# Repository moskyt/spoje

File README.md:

# Spoje

## Hardware

### Napajeni

vsechna ctyri napeti maji svoji indikaci na prednim panelu a svuj vypinac

na vstupnich 230VAC je pojistka

POZOR! IEC konektor na vstupu nema standardizovane zapojeni, resp. ruzne kabely jsou ruzne. je tedy treba mit na pameti, ze L a N mohou byt prohozene (a nikdo s tim nic neudela)

### DC

Meanwell RD-35B (+5/+24V)

5V napaji arduino

24V napaji telefonni linku

### Trafo

pouziva se pro vyzvaneci AC

je to trafo 400->110, tedy 230->63 voltu, coz je optimalni

### Zapojeni

viz `spoje_pcb` -- projekt v kicadu

v 'doc/` je vyexportovane schema a PCB v kicadu

vsechny draty jsou popsane

## Ovladani

### Vypinace

napajeni ctyr napeti (master 230VAC, vyzvaneci trafo, dva vystupy z DC zdroje)

cervene reset tlacitko (hardware reset na RESET pinu)

### Zvoneni

zluta tlacitka jsou na vyzvaneni na prislusnych linkach. je to SW zvoneni, aktivace stavu POKE.

## Literatura

specifikace vyzvanecich tonu:

https://www.ctu.cz/sites/default/files/obsah/clanky/navrh-sitoveho-planu-signalizace-verejnych-telekomunikacnich-siti-poskytujicich-verejne-dostupnou/soubory/priloha-7-specifikace-tonu-1113656123.pdf

https://vyvoj.hw.cz/navrh-obvodu/rozhrani/telefonni-linky-v-cr-a-sr.html

https://www.ranecommercial.com/legacy/note150.html

http://home.zcu.cz/~vargaj/U%20S%20T/Telefonni%20pristroje.pdf

http://mcu.cz/news.php?extend.8
http://mcu.cz/images/newspost_images/00/26/00-26.pdf

https://forum.arduino.cc/t/intercom-using-two-old-dial-telephones/606457

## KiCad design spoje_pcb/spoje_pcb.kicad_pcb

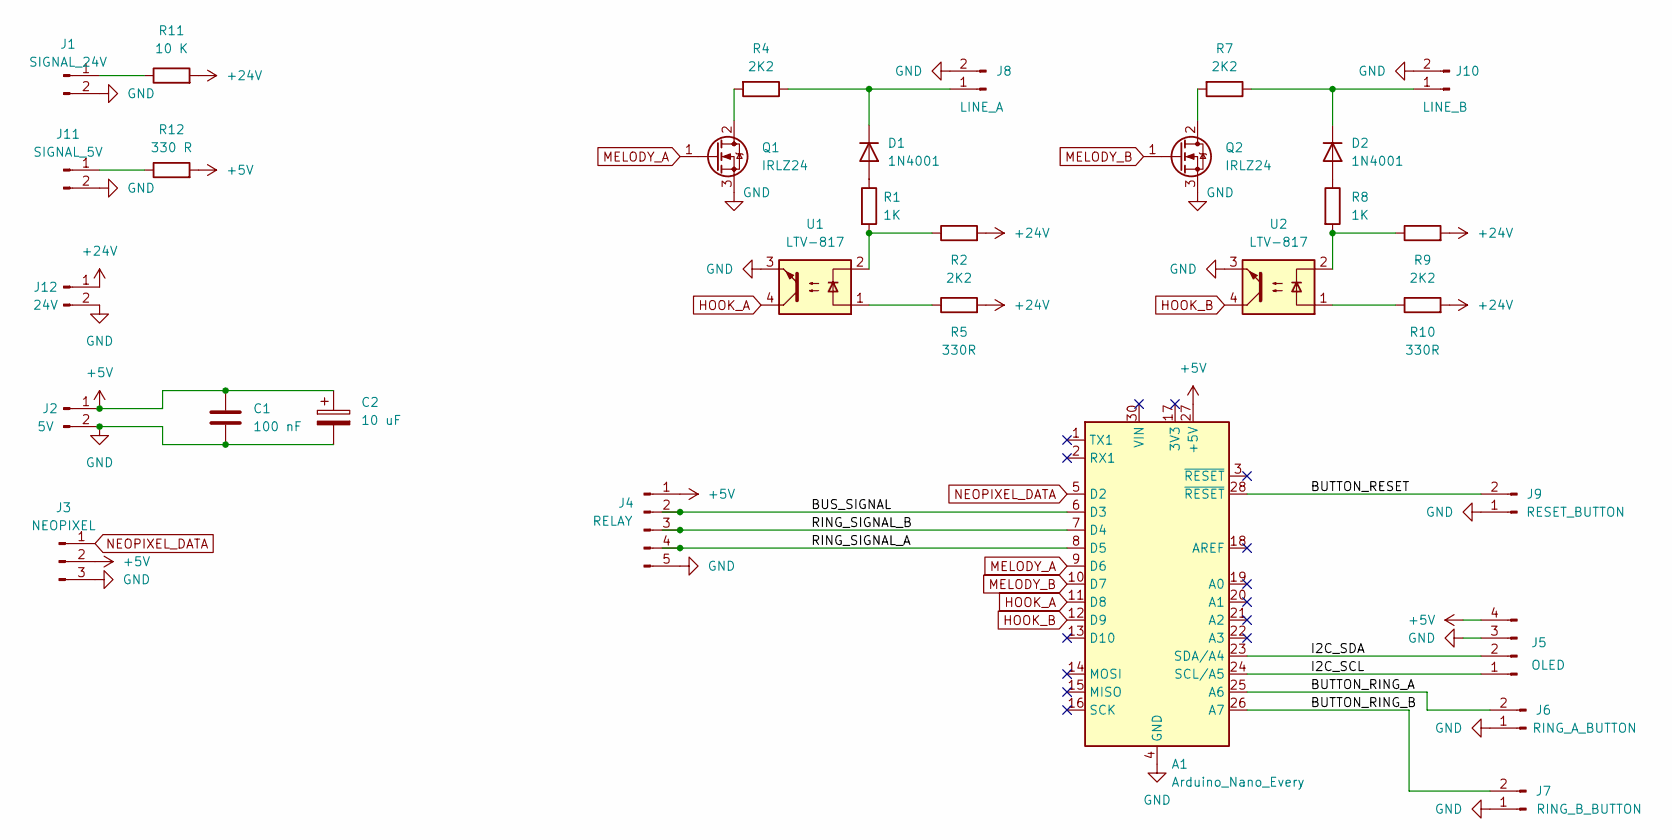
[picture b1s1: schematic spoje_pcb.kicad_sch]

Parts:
A1: Arduino_Nano_Every; Arduino_Nano
C1: 100 nF; C_Radial_D6.3mm_H5.0mm_P2.50mm
C2: 10 uF; C_Radial_D6.3mm_H5.0mm_P2.50mm
D1, D2: 1N4001; D_DO-41_SOD81_P10.16mm_Horizontal
J1: SIGNAL_24V; PinHeader_1x02_P2.54mm_Vertical
J2: 5V; JST_XH_B2B-XH-A_1x02_P2.50mm_Vertical
J3: NEOPIXEL; PinHeader_1x03_P2.54mm_Vertical
J4: RELAY; PinHeader_1x05_P2.54mm_Vertical
J5: OLED; PinHeader_1x04_P2.54mm_Vertical
J6: RING_A_BUTTON; PinHeader_1x02_P2.54mm_Vertical
J7: RING_B_BUTTON; PinHeader_1x02_P2.54mm_Vertical
J8: LINE_A; JST_XH_B2B-XH-A_1x02_P2.50mm_Vertical
J9: RESET_BUTTON; PinHeader_1x02_P2.54mm_Vertical
J10: LINE_B; JST_XH_B2B-XH-A_1x02_P2.50mm_Vertical
J11: SIGNAL_5V; PinHeader_1x02_P2.54mm_Vertical
J12: 24V; JST_XH_B2B-XH-A_1x02_P2.50mm_Vertical
Q1, Q2: IRLZ24; TO-220-3_Vertical
R1, R8: 1K; R_Axial_DIN0614_L14.3mm_D5.7mm_P20.32mm_Horizontal
R2, R9: 2K2; R_Axial_DIN0411_L9.9mm_D3.6mm_P15.24mm_Horizontal
R4, R7: 2K2; R_Axial_DIN0207_L6.3mm_D2.5mm_P10.16mm_Horizontal
R5, R10: 330R; R_Axial_DIN0207_L6.3mm_D2.5mm_P10.16mm_Horizontal
R11: 10 K; R_Axial_DIN0207_L6.3mm_D2.5mm_P10.16mm_Horizontal
R12: 330 R; R_Axial_DIN0207_L6.3mm_D2.5mm_P10.16mm_Horizontal
U1, U2: LTV-817; DIP-4_W7.62mm

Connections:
+5V: A1.27 (+5V), C1.1, C2.1, J2.1, J3.2, J4.1, J5.4, R12.2
+24V: J12.1, R2.2, R5.2, R9.2, R10.2, R11.2
/BUS_SIGNAL: A1.6 (D3), J4.2
/BUTTON_RESET: A1.28 (~RESET), J9.2
/BUTTON_RING_A: A1.25 (A6), J6.2
/BUTTON_RING_B: A1.26 (A7), J7.2
/I2C_SCL: A1.24 (SCL/A5), J5.1
/I2C_SDA: A1.23 (SDA/A4), J5.2
/RING_SIGNAL_A: A1.7 (D4), J4.3
/RING_SIGNAL_B: A1.8 (D5), J4.4
GND: A1.4 (GND), A1.29 (GND), C1.2, C2.2, J1.2, J2.2, J3.3, J4.5, J5.3, J6.1, J7.1, J8.2, J9.1, J10.2, J11.2, J12.2, Q1.3 (S), Q2.3 (S), U1.3, U2.3
HOOK_A: A1.11 (D8), U1.4
HOOK_B: A1.12 (D9), U2.4
MELODY_A: A1.9 (D6), Q1.1 (G)
MELODY_B: A1.10 (D7), Q2.1 (G)
NEOPIXEL_DATA: A1.5 (D2), J3.1
unnamed: D1.2 (A), R1.1
unnamed: D1.1 (K), J8.1, R4.1
unnamed: D2.2 (A), R8.1
unnamed: D2.1 (K), J10.1, R7.1
unnamed: J1.1, R11.1
unnamed: J11.1, R12.1
unnamed: Q1.2 (D), R4.2
unnamed: Q2.2 (D), R7.2
unnamed: R1.2, R2.1, U1.2
unnamed: R5.1, U1.1
unnamed: R8.2, R9.1, U2.2
unnamed: R10.1, U2.1

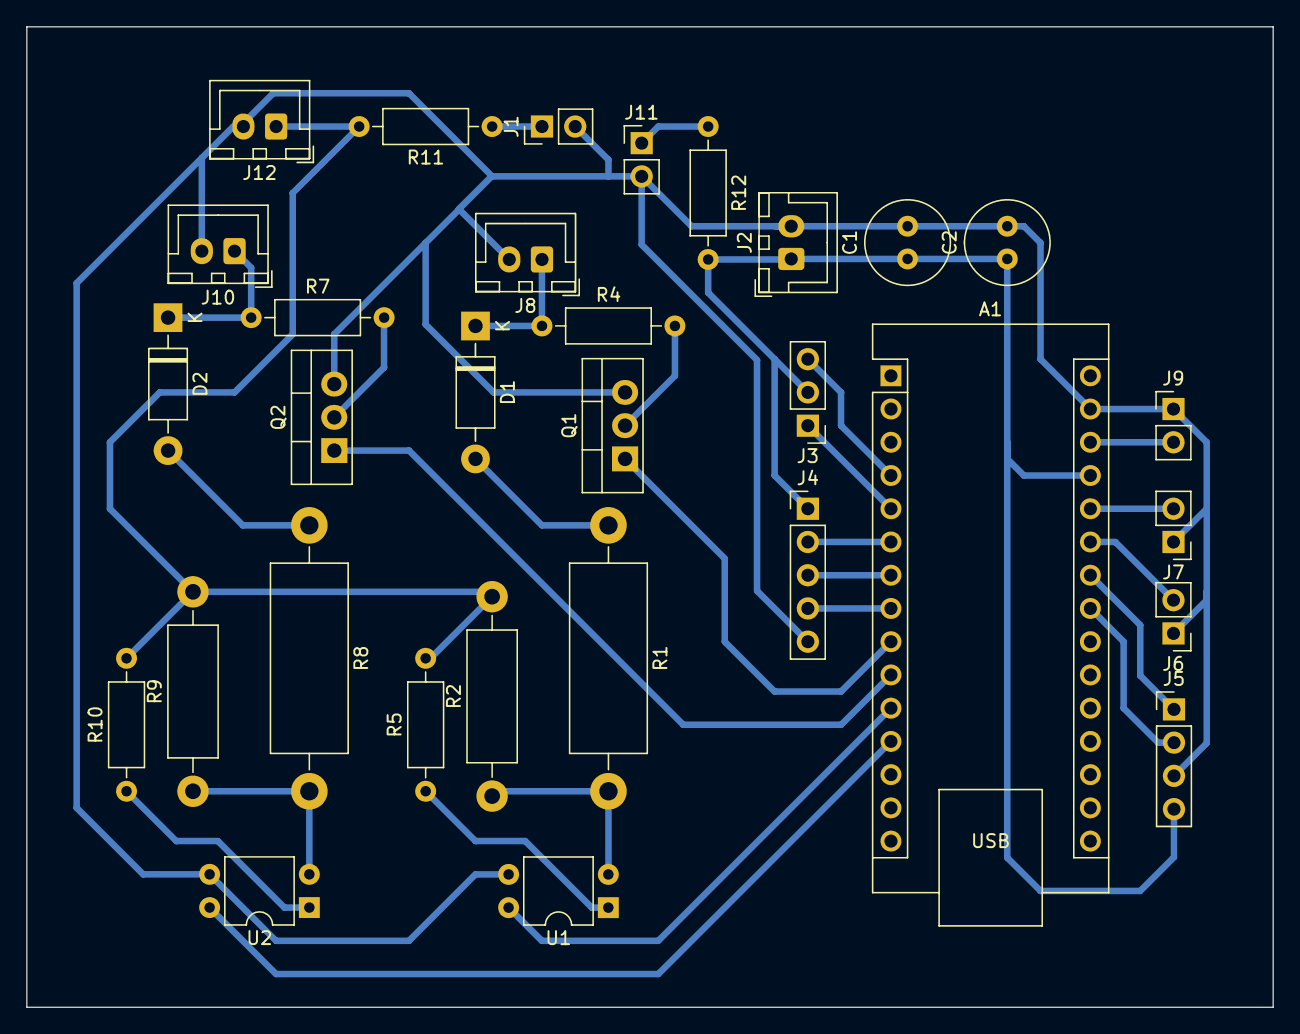
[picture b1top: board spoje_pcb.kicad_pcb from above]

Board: 2 copper layers, 95.2 x 74.9 mm, 31 parts (0 on the bottom side), 28 nets.

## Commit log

2023-07-16 add pcb in pdf
2023-07-16 some basic docs. fixed tone freqs
